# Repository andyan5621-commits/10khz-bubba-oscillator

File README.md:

# 10 kHz Bubba sine wave oscillator

A personal analog electronics project by **Andi An**, from analytical design and LTspice optimization to a working breadboard and an assembled R1 PCB.

**Final implementation documented 22 November 2026.** The R1 board has been manufactured, assembled and bench tested. Reported output is approximately **10.006 kHz**, adjustable from near zero to approximately **4.6 Vpp** into a high-impedance load, using external **±15 V** rails.

## Start here

- **[Final project report](docs/report/final-project-report.md)** — design, simulations, PCB engineering, assembly, measurements and limitations.
- [Hardware measurement record](pcb/R1/reports/hardware-measurement-log.md) and [machine-readable results](results/hardware/README.md).
- [Original PCB spectra and photographs](evidence/hardware/2026-11-20/README.md).
- [PCB source and manufacturing package](pcb/README.md).
- [Detailed soldering guide](pcb/R1/assembly/R1-detailed-soldering-guide.md) and [clear component map](pcb/R1/assembly/drawings/clear-map/R1-clear-component-map.pdf).

## Results and their scope

| Evaluation | Frequency | Output | Spectral evidence |
|---|---:|---:|---|
| Saved discrete LTspice winner | 9,984.352 Hz | 4.949660 Vpp | 90.783 dB modeled SFDR; variant without hardware pot loading |
| PCB pot-loaded simulation | approximately 9,984.35 Hz | 4.6424 Vpp | approximately 90.78 dB modeled SFDR |
| Breadboard at matching output | 10,052.85 Hz | approximately 4.40 Vpp | 91.08 dB recorded cursor separation |
| PCB three repeated captures | 10,006.08–10,006.29 Hz | calculated 4.40 Vpp | 89.70–90.67 dB selected-component cursor separation |

The PCB is closer to nominal frequency in this comparison. **Calibrated intrinsic SFDR ≥75 or ≥80 dBc has not been established.** The approximately 90 dB readings compare selected components; largest-spur selection and measurement-system residual remain unqualified. No spectral improvement over the breadboard is claimed. Timed drift and startup tests were not completed. Read the report before interpreting these figures as specifications.

## Circuit

Four buffered RC sections and a diode-limited gain stage form the Bubba oscillator. An isolation buffer feeds a resonant unity-gain Sallen–Key low-pass filter, followed by an output buffer, fixed divider and 10 kΩ linear output pot. Four OPA1656 duals provide seven signal-path channels and one grounded spare follower. The wiper output requires a high-impedance load; do not use a 50 Ω termination as an equivalent test condition.

The R1 board preserves the optimized component values. It is **95 × 79 mm**, two-layer FR-4, nominal 1.6 mm / 35 µm copper / ENIG. Archived ERC, DRC, unconnected and schematic-parity counts are zero. Independent design and fabrication review passed. These checks do not certify every physical solder joint or measured performance.

## Repository map

| Location | Contents |
|---|---|
| [Final report](docs/report/final-project-report.md) | Canonical end-project documentation |
| [Design notes](docs/design.md) | Effective values and development history |
| [Measurement overview](docs/measurements.md) | Breadboard and PCB evidence and limitations |
| [Simulation](docs/simulation.md) | Reproduction instructions, variants and models |
| [Results](results/README.md) | Saved simulation results and hardware CSV transcriptions |
| [Evidence](evidence/README.md) | Demonstration video, spectra and assembled-board photos |
| [PCB](pcb/README.md) | KiCad sources, BOM, released Gerbers, assembly and review |
| [Documentation index](docs/README.md) | Current documents versus historical records |
| [Change history](CHANGELOG.md) | Documentation milestones |

## Reproduce the simulations

The simulation tools were developed for Windows with LTspice installed. Linux/Wine simulation execution has not been validated. From the repository root:

```powershell
python -m venv .venv
.\.venv\Scripts\python.exe -m pip install -r requirements.txt
.\.venv\Scripts\python.exe simulation/scripts/Buildable_sweep.py --dry-run
.\.venv\Scripts\python.exe simulation/scripts/Measure_Oscillator_Final.py
.\.venv\Scripts\python.exe simulation/scripts/Buildable_sweep.py --check
```

Open `simulation/ltspice/Oscillator_Final.asc` for the final original schematic. See [simulation documentation](docs/simulation.md) before comparing circuit variants. Saved results were not rerun for this publication update. Historical timing corners include 46 of 256 frequency failures; no unconditional ±1% production tolerance is claimed.

## Build and use

Start with [the R1 overview](pcb/R1/README.md). Use the portable KiCad source and only the explicitly released manufacturing archive. Follow the assembly guide, current-limited power-up procedure and polarity checks before applying ±15 V. Keep the original reviewed snapshot intact when making a future revision, and rerun the relevant design checks after changes.

The [older Word report](docs/report/Oscillator_lab_report_performance_complete.docx) and dated procurement/review documents remain historical evidence, not the current project status or live supplier quotes. No open-source license has been selected. Third-party model notices remain in place; see [third-party notices](THIRD_PARTY_NOTICES.md).

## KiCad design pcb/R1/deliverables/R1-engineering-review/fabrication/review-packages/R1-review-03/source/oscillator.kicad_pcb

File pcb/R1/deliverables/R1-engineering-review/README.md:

# Oscillator PCB — R1 engineering review

**Engineering checks passed; awaiting your final fabrication approval. No order has been placed.**

The native KiCad design preserves the recovered working oscillator and confirmed prototype values. It uses the approved Alps RK09K1130A5R potentiometer, exact reserved through-hole parts, 44 physical resistor elements and eight bare probe pads.

- [Final engineering summary](reports/final-engineering-summary.md)
- [Independent verification](verification/independent-review.md)
- [Fabrication export inspection](reports/export-inspection.md)
- [Open the portable KiCad project](fabrication/review-packages/R1-review-03/source/oscillator.kicad_pro)
- [Gerber/drill review ZIP](fabrication/review-packages/R1-review-03/R1-review-03-gerbers-UNRELEASED.zip)
- [Per-component BOM](bom/per-component.csv), [grouped BOM](bom/grouped-bom.csv), [procurement quantities](bom/draft_bom.csv)
- [Assembly and test instructions](assembly/assembly-and-test.md)
- [Printable schematic](assembly/drawings/schematic-R1.pdf), [placement drawing](assembly/drawings/placement-R1.pdf)
- [Task board](reports/task-board.md), [decisions](reports/decision-log.md), [risks](reports/risk-register.md)

The board is 95 × 79 mm, two layers, nominal 1.6 mm FR-4 / 35 µm copper / ENIG. Final ERC, DRC, unconnected and native schematic-parity counts are all zero. Independent engineering package review passed; ordinary incoming fit and physical performance validation remain required. Earlier review-01/02 directories are superseded and are not manufacturing inputs.

The `source` folder in the final candidate keeps the project, schematic, board, rules and custom libraries together for KiCad 9. Working directories remain under schematic/ and pcb/; the candidate is an immutable reviewed snapshot. Do not edit the snapshot and then reuse its checks or hashes.

No new PCB has been physically tested. Simulated SFDR is not measured hardware performance. The intended October 31 assembly date depends on the live manufacturing/shipping quote and parts receipt; it is not guaranteed. Both final fabrication release and any purchase require explicit user approval.

## Delivery contents and integrity

This consolidated delivery contains the immutable R1-review-03 candidate and the final independent review and operating documentation. Open the native KiCad project through the link above. Only the Gerber/drill ZIP is the proposed fabrication input; do not upload this complete documentation archive to order boards. Follow [ordering guidance](fabrication/ordering-guidance.md).

The candidate's original SHA256.json applies relative to its own directory. The outer SHA256.json covers every delivered file except itself. Reports retain workspace-relative evidence references; detailed simulation waveforms and intermediate engineering history remain in the version-controlled project workspace rather than this delivery.

The parasitic-risk report records an earlier request to rework VOUT. The final design removes its redundant loop; the remaining route was reviewed and accepted in decision D017 and the final independent report. Some capacitor, connector and potentiometer body models are absent from the 3D preview, which is not an enclosure-fit model.

Gates A–D passed. User fabrication release, live quote approval, incoming fit checks, assembly and measured hardware validation remain outstanding. No upload, order or physical PCB test has occurred.

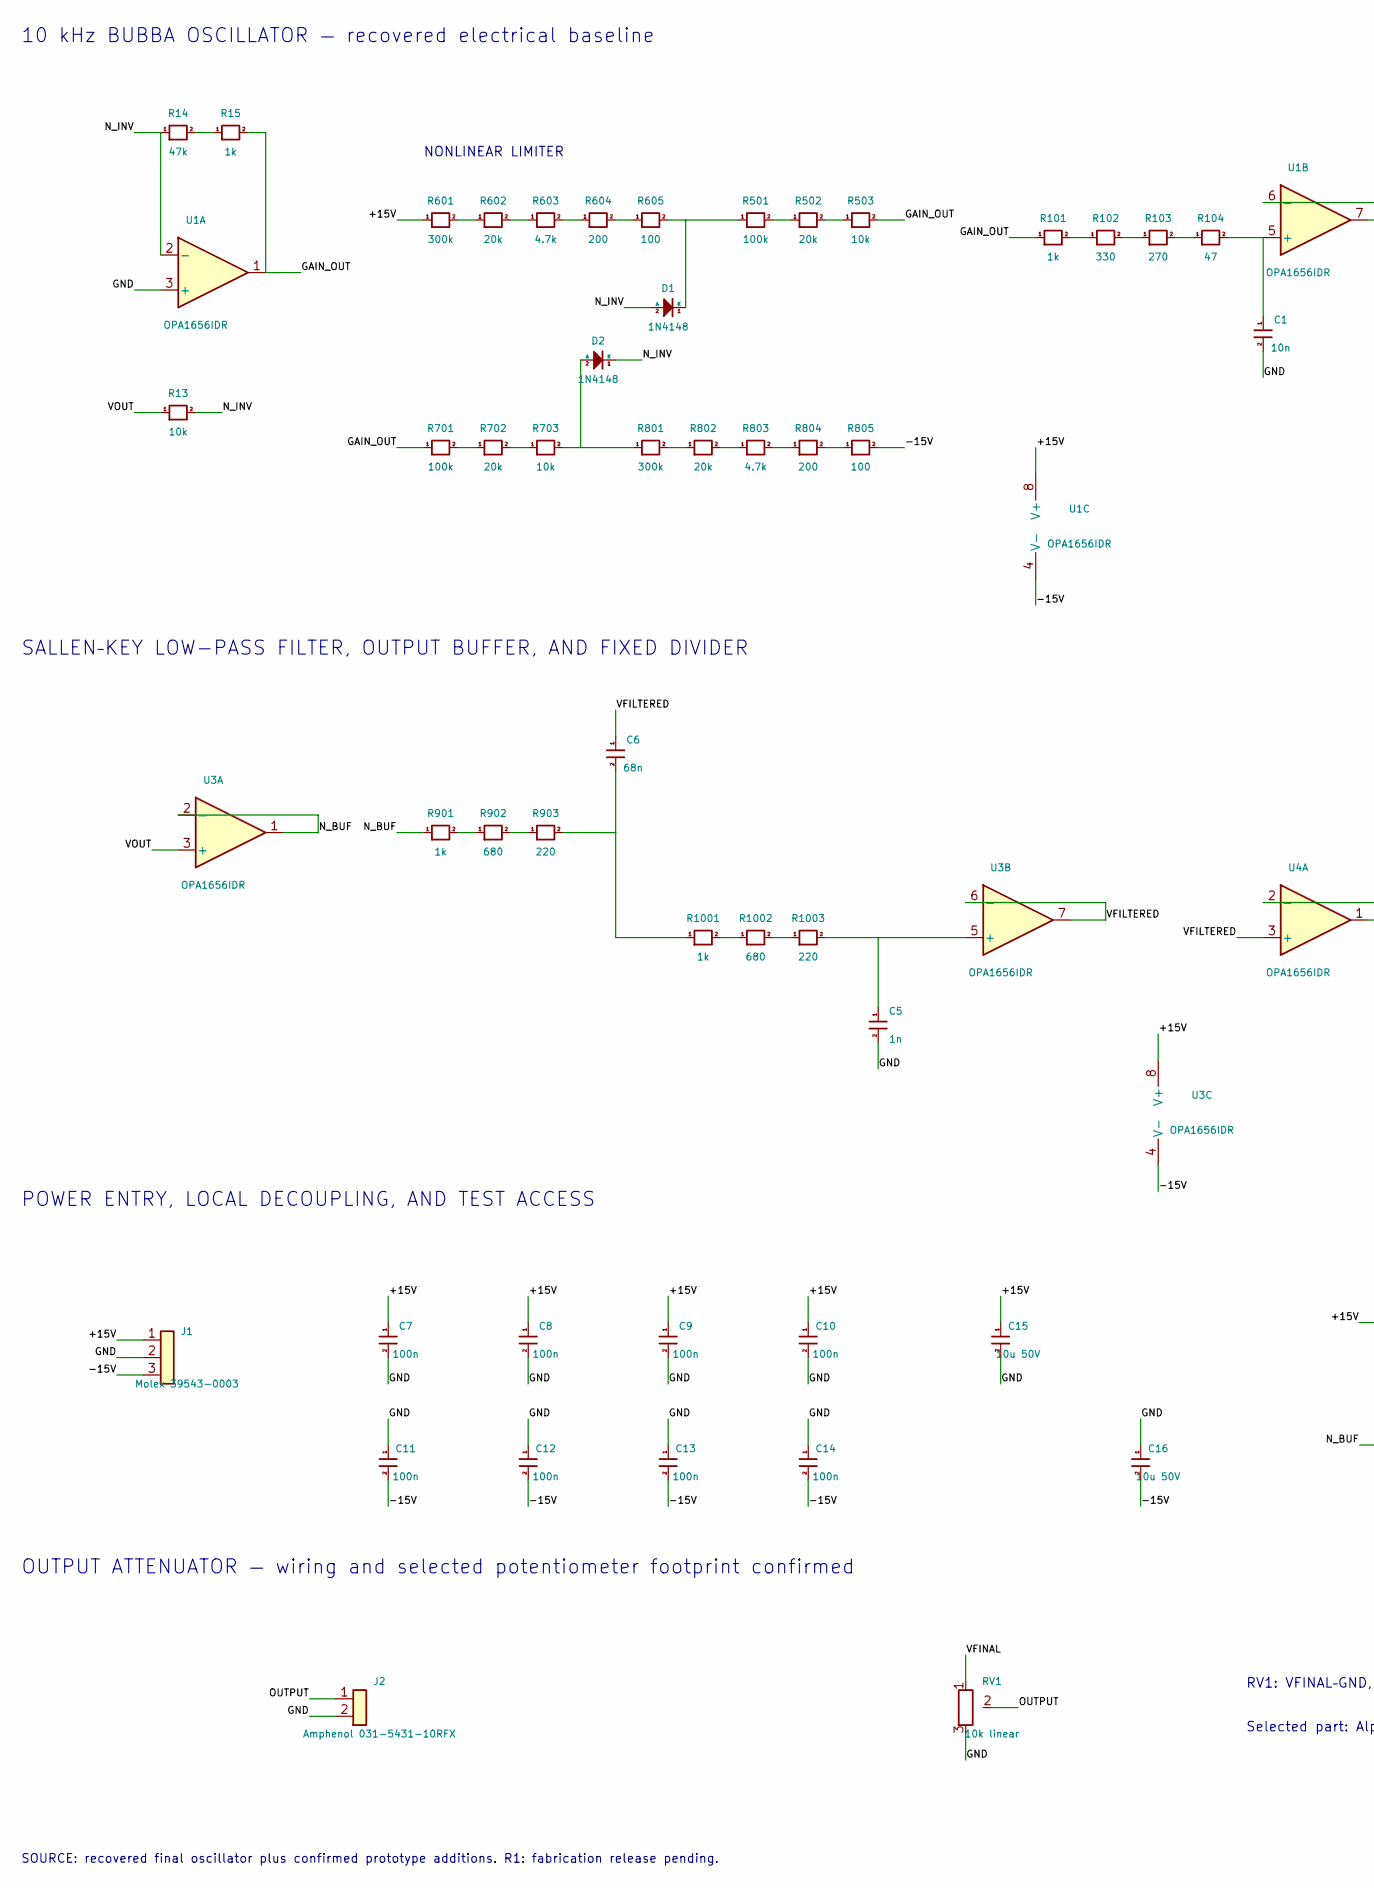
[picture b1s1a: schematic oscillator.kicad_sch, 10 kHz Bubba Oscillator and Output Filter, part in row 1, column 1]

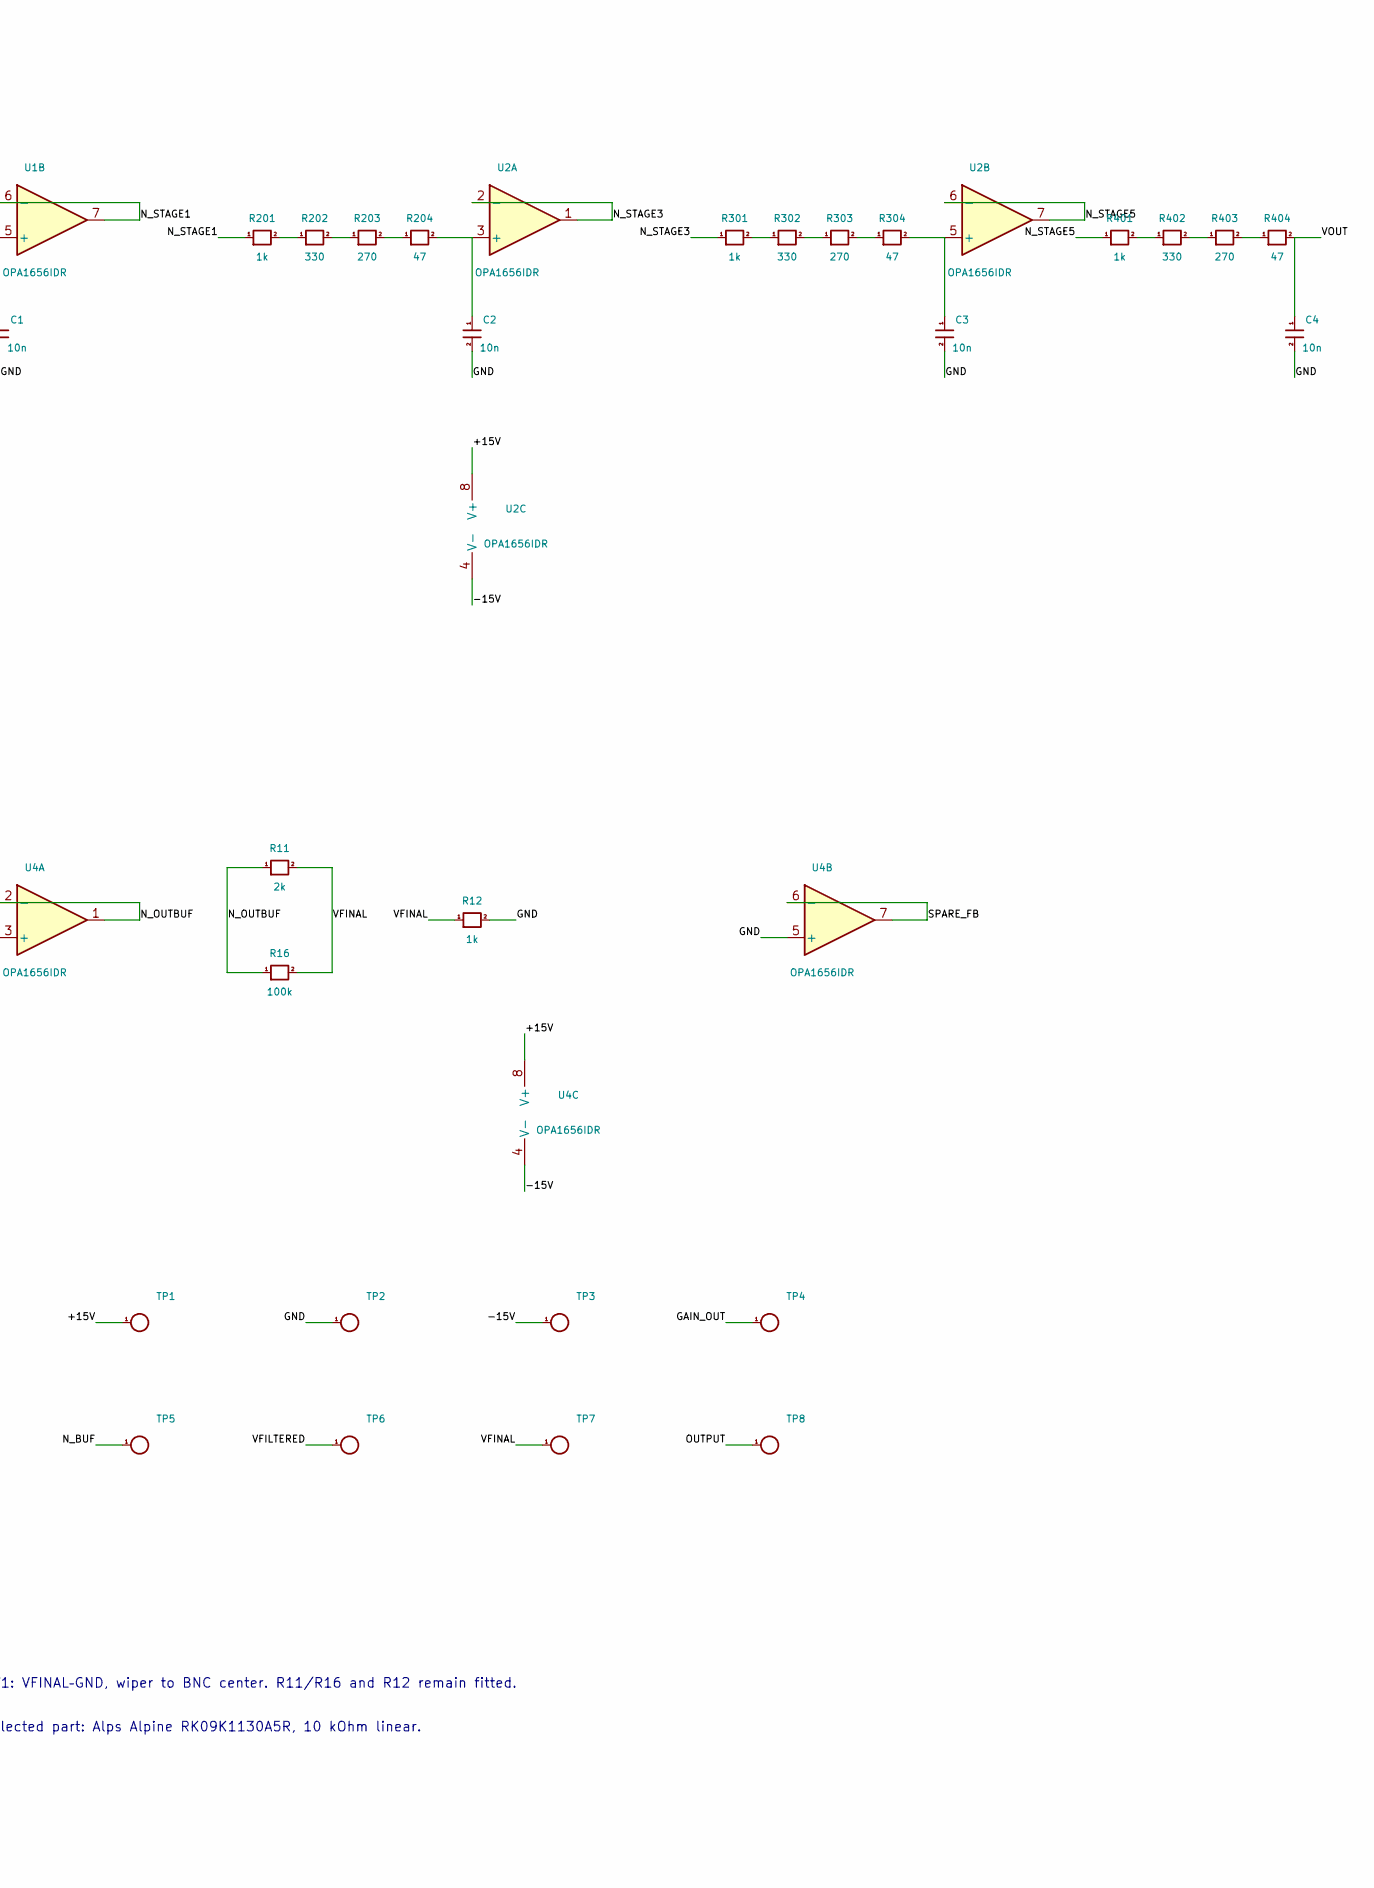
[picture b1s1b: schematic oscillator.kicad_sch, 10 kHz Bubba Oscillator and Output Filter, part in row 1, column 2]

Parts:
C1, C2, C3, C4: 10n; C_Vishay_MKP1837310011_P5; MPN MKP1837310011
C5: 1n; C_AVX_SR215A102FARTR1_P5.08; MPN SR215A102FARTR1
C6: 68n; C_Vishay_MKP1837368011_P5; MPN MKP1837368011
C7: 100n; C_KEMET_C315_P2.54_RoutedSilk; MPN C315C104K5R5TA
C8, C9, C10, C11, C12, C13, C14: 100n; C_KEMET_C315C104K5R5TA_P2.54; MPN C315C104K5R5TA
C15, C16: 10u 50V; CP_Radial_D5.0mm_P2.00mm; MPN EEU-FR1H100
D1, D2: 1N4148; D_DO-35_SOD27_P7.62mm_Horizontal; MPN 1N4148
J1: Molex 39543-0003; J_Molex_39543-0003_Draft; MPN 39543-0003
J2: Amphenol 031-5431-10RFX; J_Amphenol_031-5431-10RFX_Draft; MPN 031-5431-10RFX
R11: 2k; R_0805_2012Metric_Pad1.20x1.40mm_HandSolder
R12, R15, R101, R201, R301, R401, R901, R1001: 1k; R_0805_2012Metric_Pad1.20x1.40mm_HandSolder
R13, R503, R703: 10k; R_0805_2012Metric_Pad1.20x1.40mm_HandSolder
R14: 47k; R_0805_2012Metric_Pad1.20x1.40mm_HandSolder
R16, R501, R701: 100k; R_0805_2012Metric_Pad1.20x1.40mm_HandSolder
R102, R202, R302, R402: 330; R_0805_2012Metric_Pad1.20x1.40mm_HandSolder
R103, R203, R303, R403: 270; R_0805_2012Metric_Pad1.20x1.40mm_HandSolder
R104, R204, R304, R404: 47; R_0805_2012Metric_Pad1.20x1.40mm_HandSolder
R502, R602, R702, R802: 20k; R_0805_2012Metric_Pad1.20x1.40mm_HandSolder
R601, R801: 300k; R_0805_2012Metric_Pad1.20x1.40mm_HandSolder
R603, R803: 4.7k; R_0805_2012Metric_Pad1.20x1.40mm_HandSolder
R604, R804: 200; R_0805_2012Metric_Pad1.20x1.40mm_HandSolder
R605, R805: 100; R_0805_2012Metric_Pad1.20x1.40mm_HandSolder
R902, R1002: 680; R_0805_2012Metric_Pad1.20x1.40mm_HandSolder
R903, R1003: 220; R_0805_2012Metric_Pad1.20x1.40mm_HandSolder
RV1: 10k linear; Potentiometer_Alps_RK09K_Single_Vertical; MPN RK09K1130A5R
TP1: +15V; TestPoint_Pad_D1.5mm
TP2: GND; TestPoint_Pad_D1.5mm
TP3: -15V; TestPoint_Pad_D1.5mm
TP4: GAIN_OUT; TestPoint_Pad_D1.5mm
TP5: N_BUF; TestPoint_Pad_D1.5mm
TP6: VFILTERED; TestPoint_Pad_D1.5mm
TP7: VFINAL; TestPoint_Pad_D1.5mm
TP8: OUTPUT; TestPoint_Pad_D1.5mm
U1, U2, U4: OPA1656IDR; SOIC-8_3.9x4.9mm_P1.27mm; MPN OPA1656IDR
U3: OPA1656IDR; SOIC-8_3.9x4.9mm_P1.27mm_RoutedSilk; MPN OPA1656IDR

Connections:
/+15V: C7.1, C8.1, C9.1, C10.1, C15.1 (+), J1.1, R601.1, TP1.1, U1.8 (V+), U2.8 (V+), U3.8 (V+), U4.8 (V+)
/-15V: C11.2, C12.2, C13.2, C14.2, C16.2 (-), J1.3, R805.2, TP3.1, U1.4 (V-), U2.4 (V-), U3.4 (V-), U4.4 (V-)
/GAIN_OUT: R15.2, R101.1, R503.2, R701.1, TP4.1, U1.1
/GND: C1.2, C2.2, C3.2, C4.2, C5.2, C7.2, C8.2, C9.2, C10.2, C11.1, C12.1, C13.1, C14.1, C15.2 (-), C16.1 (+), J1.2, J2.2, R12.2, RV1.3, TP2.1, U1.3 (+), U4.5 (+)
/N_BUF: R901.1, TP5.1, U3.1, U3.2 (-)
/N_INV: D1.2 (A), D2.1 (K), R13.2, R14.1, U1.2 (-)
/N_OUTBUF: R11.1, R16.1, U4.1, U4.2 (-)
/N_STAGE1: R201.1, U1.6 (-), U1.7
/N_STAGE3: R301.1, U2.1, U2.2 (-)
/N_STAGE5: R401.1, U2.6 (-), U2.7
/OUTPUT: J2.1, RV1.2, TP8.1
/SPARE_FB: U4.6 (-), U4.7
/VFILTERED: C6.1, TP6.1, U3.6 (-), U3.7, U4.3 (+)
/VFINAL: R11.2, R12.1, R16.2, RV1.1, TP7.1
/VOUT: C4.1, R13.1, R404.2, U3.3 (+)
unnamed: C6.2, R903.2, R1001.1
unnamed: D1.1 (K), R501.1, R605.2
unnamed: D2.2 (A), R703.2, R801.1
unnamed: R14.2, R15.1
unnamed: R101.2, R102.1
unnamed: R102.2, R103.1
unnamed: R103.2, R104.1
unnamed: R201.2, R202.1
unnamed: R202.2, R203.1
unnamed: R203.2, R204.1
unnamed: R301.2, R302.1
unnamed: R302.2, R303.1
unnamed: R303.2, R304.1
unnamed: R401.2, R402.1
unnamed: R402.2, R403.1
unnamed: R403.2, R404.1
unnamed: R501.2, R502.1
unnamed: R502.2, R503.1
unnamed: R601.2, R602.1
unnamed: R602.2, R603.1
unnamed: R603.2, R604.1
unnamed: R604.2, R605.1
unnamed: R701.2, R702.1
unnamed: R702.2, R703.1
unnamed: R801.2, R802.1
unnamed: R802.2, R803.1
unnamed: R803.2, R804.1
unnamed: R804.2, R805.1
unnamed: R901.2, R902.1
unnamed: R902.2, R903.1
unnamed: R1001.2, R1002.1
unnamed: R1002.2, R1003.1
unnamed: C1.1, R104.2, U1.5 (+)
unnamed: C2.1, R204.2, U2.3 (+)
unnamed: C3.1, R304.2, U2.5 (+)
unnamed: C5.1, R1003.2, U3.5 (+)

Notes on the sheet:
10 kHz BUBBA OSCILLATOR — recovered electrical baseline
NONLINEAR LIMITER
SALLEN–KEY LOW-PASS FILTER, OUTPUT BUFFER, AND FIXED DIVIDER
POWER ENTRY, LOCAL DECOUPLING, AND TEST ACCESS
OUTPUT ATTENUATOR — wiring and selected potentiometer footprint confirmed
RV1: VFINAL–GND, wiper to BNC center. R11/R16 and R12 remain fitted.
Selected part: Alps Alpine RK09K1130A5R, 10 kOhm linear.
SOURCE: recovered final oscillator plus confirmed prototype additions. R1: fabrication release pending.

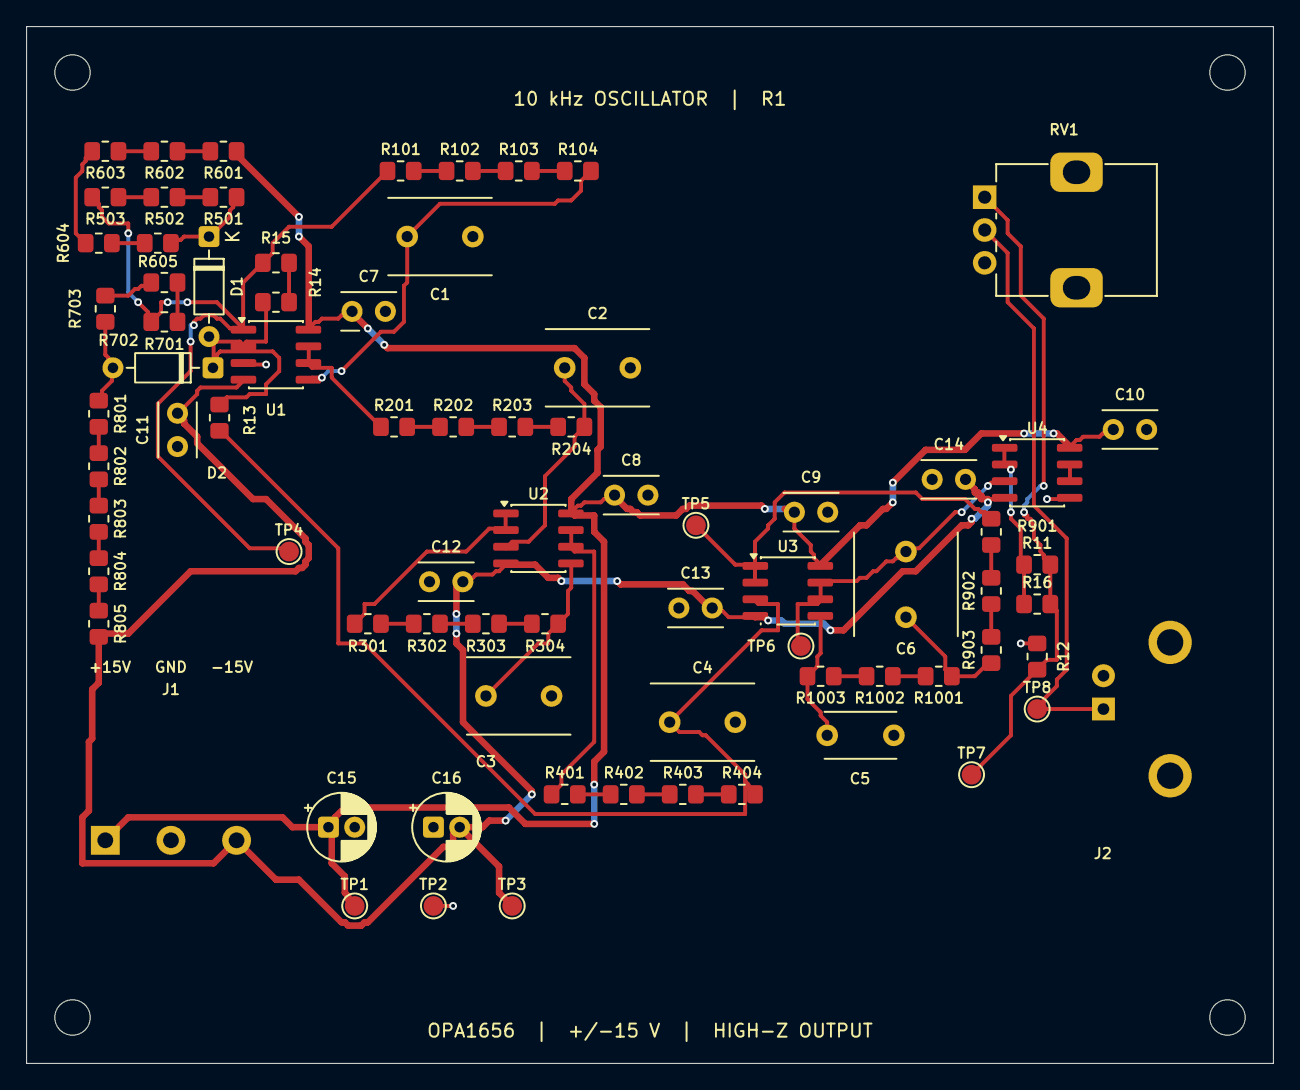
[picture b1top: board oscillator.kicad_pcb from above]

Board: 2 copper layers, 95.0 x 79.0 mm, 81 parts (0 on the bottom side), 51 nets.

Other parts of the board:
H1, H2, H3, H4: M2.5 / 2.7 mm NPTH; MountingHole_2.7mm_M2.5

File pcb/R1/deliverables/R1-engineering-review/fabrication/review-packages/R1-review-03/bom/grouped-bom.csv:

References,Value,Manufacturer,MPN,Footprint,Fitted_quantity,Status
"C1, C2, C3, C4",10n,Vishay,MKP1837310011,Oscillator:C_Vishay_MKP1837310011_P5,4,SELECTED_NOT_RELEASED
C5,1n,KYOCERA AVX,SR215A102FARTR1,Oscillator:C_AVX_SR215A102FARTR1_P5.08,1,SELECTED_NOT_RELEASED
C6,68n,Vishay,MKP1837368011,Oscillator:C_Vishay_MKP1837368011_P5,1,SELECTED_NOT_RELEASED
C7,100n,KEMET,C315C104K5R5TA,Oscillator:C_KEMET_C315_P2.54_RoutedSilk,1,SELECTED_NOT_RELEASED
"C8, C9, C10, C11, C12, C13, C14",100n,KEMET,C315C104K5R5TA,Oscillator:C_KEMET_C315C104K5R5TA_P2.54,7,SELECTED_NOT_RELEASED
"C15, C16",10u 50V,Panasonic,EEU-FR1H100,Capacitor_THT:CP_Radial_D5.0mm_P2.00mm,2,SELECTED_NOT_RELEASED
"D1, D2",1N4148,onsemi,1N4148,Diode_THT:D_DO-35_SOD27_P7.62mm_Horizontal,2,SELECTED_NOT_RELEASED
J1,Molex 39543-0003,Molex,39543-0003,Oscillator:J_Molex_39543-0003_Draft,1,SELECTED_NOT_RELEASED
J2,Amphenol 031-5431-10RFX,Amphenol RF,031-5431-10RFX,Oscillator:J_Amphenol_031-5431-10RFX_Draft,1,SELECTED_NOT_RELEASED
R11,2k,YAGEO,RT0805BRD072KL,Resistor_SMD:R_0805_2012Metric_Pad1.20x1.40mm_HandSolder,1,SELECTED_NOT_RELEASED
"R12, R15, R101, R201, R301, R401, R901, R1001",1k,YAGEO,RT0805BRD071KL,Resistor_SMD:R_0805_2012Metric_Pad1.20x1.40mm_HandSolder,8,SELECTED_NOT_RELEASED
"R13, R503, R703",10k,YAGEO,RT0805BRD0710KL,Resistor_SMD:R_0805_2012Metric_Pad1.20x1.40mm_HandSolder,3,SELECTED_NOT_RELEASED
R14,47k,Vishay Dale,TNPW080547K0BEEA,Resistor_SMD:R_0805_2012Metric_Pad1.20x1.40mm_HandSolder,1,SELECTED_NOT_RELEASED
"R16, R501, R701",100k,YAGEO,RT0805BRD07100KL,Resistor_SMD:R_0805_2012Metric_Pad1.20x1.40mm_HandSolder,3,SELECTED_NOT_RELEASED
"R102, R202, R302, R402",330,YAGEO,RT0805BRD07330RL,Resistor_SMD:R_0805_2012Metric_Pad1.20x1.40mm_HandSolder,4,SELECTED_NOT_RELEASED
"R103, R203, R303, R403",270,YAGEO,RT0805BRD07270RL,Resistor_SMD:R_0805_2012Metric_Pad1.20x1.40mm_HandSolder,4,SELECTED_NOT_RELEASED
"R104, R204, R304, R404",47,YAGEO,RT0805BRD0747RL,Resistor_SMD:R_0805_2012Metric_Pad1.20x1.40mm_HandSolder,4,SELECTED_NOT_RELEASED
"R502, R602, R702, R802",20k,YAGEO,RT0805BRD0720KL,Resistor_SMD:R_0805_2012Metric_Pad1.20x1.40mm_HandSolder,4,SELECTED_NOT_RELEASED
"R601, R801",300k,YAGEO,RT0805BRD07300KL,Resistor_SMD:R_0805_2012Metric_Pad1.20x1.40mm_HandSolder,2,SELECTED_NOT_RELEASED
"R603, R803",4.7k,YAGEO,RT0805BRD074K7L,Resistor_SMD:R_0805_2012Metric_Pad1.20x1.40mm_HandSolder,2,SELECTED_NOT_RELEASED
"R604, R804",200,YAGEO,RT0805BRD07200RL,Resistor_SMD:R_0805_2012Metric_Pad1.20x1.40mm_HandSolder,2,SELECTED_NOT_RELEASED
"R605, R805",100,YAGEO,RT0805BRD07100RL,Resistor_SMD:R_0805_2012Metric_Pad1.20x1.40mm_HandSolder,2,SELECTED_NOT_RELEASED
"R902, R1002",680,YAGEO,RT0805BRD07680RL,Resistor_SMD:R_0805_2012Metric_Pad1.20x1.40mm_HandSolder,2,SELECTED_NOT_RELEASED
"R903, R1003",220,YAGEO,RT0805BRD07220RL,Resistor_SMD:R_0805_2012Metric_Pad1.20x1.40mm_HandSolder,2,SELECTED_NOT_RELEASED
RV1,10k linear,Alps Alpine,RK09K1130A5R,Potentiometer_THT:Potentiometer_Alps_RK09K_Single_Vertical,1,SELECTED_NOT_RELEASED
TP1,+15V,PCB fabrication,BARE_PCB_PROBE_PAD,TestPoint:TestPoint_Pad_D1.5mm,1,NO_PURCHASE
TP2,GND,PCB fabrication,BARE_PCB_PROBE_PAD,TestPoint:TestPoint_Pad_D1.5mm,1,NO_PURCHASE
TP3,-15V,PCB fabrication,BARE_PCB_PROBE_PAD,TestPoint:TestPoint_Pad_D1.5mm,1,NO_PURCHASE
TP4,GAIN_OUT,PCB fabrication,BARE_PCB_PROBE_PAD,TestPoint:TestPoint_Pad_D1.5mm,1,NO_PURCHASE
TP5,N_BUF,PCB fabrication,BARE_PCB_PROBE_PAD,TestPoint:TestPoint_Pad_D1.5mm,1,NO_PURCHASE
TP6,VFILTERED,PCB fabrication,BARE_PCB_PROBE_PAD,TestPoint:TestPoint_Pad_D1.5mm,1,NO_PURCHASE
TP7,VFINAL,PCB fabrication,BARE_PCB_PROBE_PAD,TestPoint:TestPoint_Pad_D1.5mm,1,NO_PURCHASE
TP8,OUTPUT,PCB fabrication,BARE_PCB_PROBE_PAD,TestPoint:TestPoint_Pad_D1.5mm,1,NO_PURCHASE
"U1, U2, U4",OPA1656IDR,Texas Instruments,OPA1656IDR,Package_SO:SOIC-8_3.9x4.9mm_P1.27mm,3,SELECTED_NOT_RELEASED
U3,OPA1656IDR,Texas Instruments,OPA1656IDR,Oscillator:SOIC-8_3.9x4.9mm_P1.27mm_RoutedSilk,1,SELECTED_NOT_RELEASED

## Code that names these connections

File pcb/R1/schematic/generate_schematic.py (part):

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s.resistor("R15", "1k", 1800, 900, None, None, "RF part 2", "47k + 1k series = 48k")
s.wire(1600, 900, 1700, 900)
s.wire(1400, 900, 1400, 1600)
s.label(1400, 900, "N_INV")
s.wire(1900, 900, 2000, 900); s.wire(2000, 900, 2000, 1700)
s.wire(2000, 1700, 2200, 1700); s.label(2200, 1700, "GAIN_OUT")
s.resistor("R13", "10k", 1500, 2500, "VOUT", "N_INV", "RG", "10k")

for ref, val, x, role in [("R601", "300k", 3000, 1), ("R602", "20k", 3300, 2),
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               "N_STAGE5" if off == 0 else None, None, f"R4 part {off+1}",
               "1k + 330 + 270 + 47 = 1647 ohm")
for off in range(3): s.wire(14200 + off * 300, 1500, 14300 + off * 300, 1500)
s.label(15100, 1500, "VOUT")
s.cap("C4", "10n", 15100, 2050, None, "GND", "Polypropylene 1%", "MKP1837310011")
s.wire(15100, 1500, 15100, 1950)
s.power_unit("U1", 6500, 3150)
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s.note(600, 3900, "SALLEN–KEY LOW-PASS FILTER, OUTPUT BUFFER, AND FIXED DIVIDER", 80)
s.opamp("U3", 1, 1800, 4900, "VOUT", None, None, "Filter input follower")
s.wire(2100, 4900, 2300, 4900); s.wire(2300, 4900, 2300, 4800); s.wire(2300, 4800, 1500, 4800)
s.label(2300, 4900, "N_BUF")
for ref, val, x in [("R901", "1k", 3000), ("R902", "680", 3300), ("R903", "220", 3600)]:
    s.resistor(ref, val, x, 4900, "N_BUF" if ref == "R901" else None, None, "R9 series", "1k + 680 + 220 = 1.9k")
s.wire(3100, 4900, 3200, 4900); s.wire(3400, 4900, 3500, 4900)
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s.cap("C5", "1n", 5500, 6000, None, "GND", "C0G/NP0 1%", "SR215A102FARTR1")
s.wire(5500, 5500, 5500, 5900)
s.wire(6600, 5400, 6800, 5400); s.wire(6800, 5400, 6800, 5300); s.wire(6800, 5300, 6000, 5300)
s.label(6800, 5400, "VFILTERED")

s.opamp("U4", 1, 8000, 5400, "VFILTERED", None, None, "Output unity follower")
s.wire(8300, 5400, 8500, 5400); s.wire(8500, 5400, 8500, 5300); s.wire(8500, 5300, 7700, 5300)
s.label(8500, 5400, "N_OUTBUF")
s.resistor("R11", "2k", 9300, 5100, None, None, "Output divider R11A", "2k || 100k = 1960.784 ohm")
s.resistor("R16", "100k", 9300, 5700, None, None, "Output divider R11B", "2k || 100k = 1960.784 ohm")
s.wire(9200, 5100, 9000, 5100); s.wire(9000, 5100, 9000, 5700); s.wire(9000, 5700, 9200, 5700)
s.wire(9400, 5100, 9600, 5100); s.wire(9600, 5100, 9600, 5700); s.wire(9600, 5700, 9400, 5700)
s.label(9000, 5400, "N_OUTBUF"); s.label(9600, 5400, "VFINAL")
s.resistor("R12", "1k", 10400, 5400, "VFINAL", "GND", "Output divider lower leg")
s.opamp("U4", 2, 12500, 5400, "GND", None, None, "Spare channel grounded follower")
s.wire(12800, 5400, 13000, 5400); s.wire(13000, 5400, 13000, 5300); s.wire(13000, 5300, 12200, 5300)
s.label(13000, 5400, "SPARE_FB")
s.power_unit("U3", 7200, 6500); s.power_unit("U4", 10800, 6500)

s.note(600, 7050, "POWER ENTRY, LOCAL DECOUPLING, AND TEST ACCESS", 80)
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s.comp("R_Potentiometer", "RV1", "10k linear", 6000, 9900,
       footprint="Potentiometer_THT:Potentiometer_Alps_RK09K_Single_Vertical",
       fields={"MPN": "RK09K1130A5R", "Manufacturer": "Alps Alpine", "Status": "User-approved documented alternate"})
s.label(6000, 9750, "VFINAL"); s.label(6000, 10050, "GND"); s.label(6150, 9900, "OUTPUT")
s.note(7600, 9800, "RV1: VFINAL–GND, wiper to BNC center. R11/R16 and R12 remain fitted.", 55)
s.note(7600, 10050, "Selected part: Alps Alpine RK09K1130A5R, 10 kOhm linear.", 55)
s.note(600, 10800, "SOURCE: recovered final oscillator plus confirmed prototype additions. R1: fabrication release pending.", 50)
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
